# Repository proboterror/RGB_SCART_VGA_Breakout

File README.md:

# JVC TM-1011G RGB SCART / VGA Breakout with S-Video

For RGB/SCART modding JVC, SONY PVM video monitors and consumer CRT TVs.

Modified version for JVC TM-1011G.

- Adjusted board mounting holes / layout.
- Added S-Video (Mini-DIN 4 pin) optional connector with 510 Ohm load resistors.
- Removed CSYNC load resistors / capacitor / solder jumper. CSYNC directly connected to output.

Continuation of [RGB SCART Breakout board](https://github.com/proboterror/RGB_SCART_Breakout).

Features:
- SCART / VGA inputs are not switchable. Simultaneous connection are NOT RECOMMENDED, use at own risk.
- Protection diodes on SCART Blanking / VGA +5V inputs against back current with 2 devices connected.
- 3.5 mm mini jack connector for SCART input.
- Optional S-Video connector.

## Schematics:<br>

## Board view:<br>

## Bill of Materials
|Reference|Value|Footprint|Qty|
|-----|-----|-----|-----|
|C1,C2,C3|100nF|0805|3|
|D1,D2|BAT54W|Diode_SMD:D_SOD-123|2|
|J1|SCART-F|CS-102 (SCART-21S)|1|
|J3|DE15 Socket / DSUB-15-HD / VGA| DSUB-15-HD_Socket_Horizontal P2.29x1.90mm EdgePinOffset3.03mm MountingHolesOffset4.94mm|1|
|J11|SJ1-3535NG|CUI/Same Sky Device SJ1-3535NG|1|
|R1,R2,R3|0R/24R/30R|0805|3|
|R6,R7,R8|75R/51R|0805|3|
|R9,R10|510R|0805|2|
|J2|Mini-DIN 4 pin socket||1|
|R11|1K/1K2/4K7|0805|1|
|R12|2.3K/2K8/10K|0805|1|

Notes:
- All resistors are 1%.
- RGB termination / voltage divider resistors values are depending on monitor jungle (chroma/deflection) IC.<br>
For jungle ICs with 0.7Vpp RGB inputs (like TDA8366):<br>
R1, R2, R3: 0 Ohm,<br>
R6, R7, R8: 75 Ohm.<br>
For jungle ICs with 0.5Vpp RGB inputs (like TA1276AN):<br>
R1, R2, R3: 30 Ohm,<br>
R6, R7, R8: 75 Ohm.<br>
Attenuation / divider resistors R1, R2, R3 can be changed to 24 Ohm, and termination resistors R6, R7, R8 to 51 Ohm for "proper" 75 Ohm termination.
- Blanking voltage divider / pulldown resistors values are depends on jungle IC requirements.<br>
For 3V inputs use R11=1K/1.2K, R12=2.3K/2.8K, and so on.<br>
Some ICs require pulldown R12=10~50K.<br>
R12 can be omitted but R11=120R~180R is recommended to limit current.
- More info on Blanking voltage divider: [sector.sunthar.com/guides/crt-rgb-mod](https://sector.sunthar.com/guides/crt-rgb-mod/rgb-mux.html#how-to-use-the-voltage-divider-on-the-board)

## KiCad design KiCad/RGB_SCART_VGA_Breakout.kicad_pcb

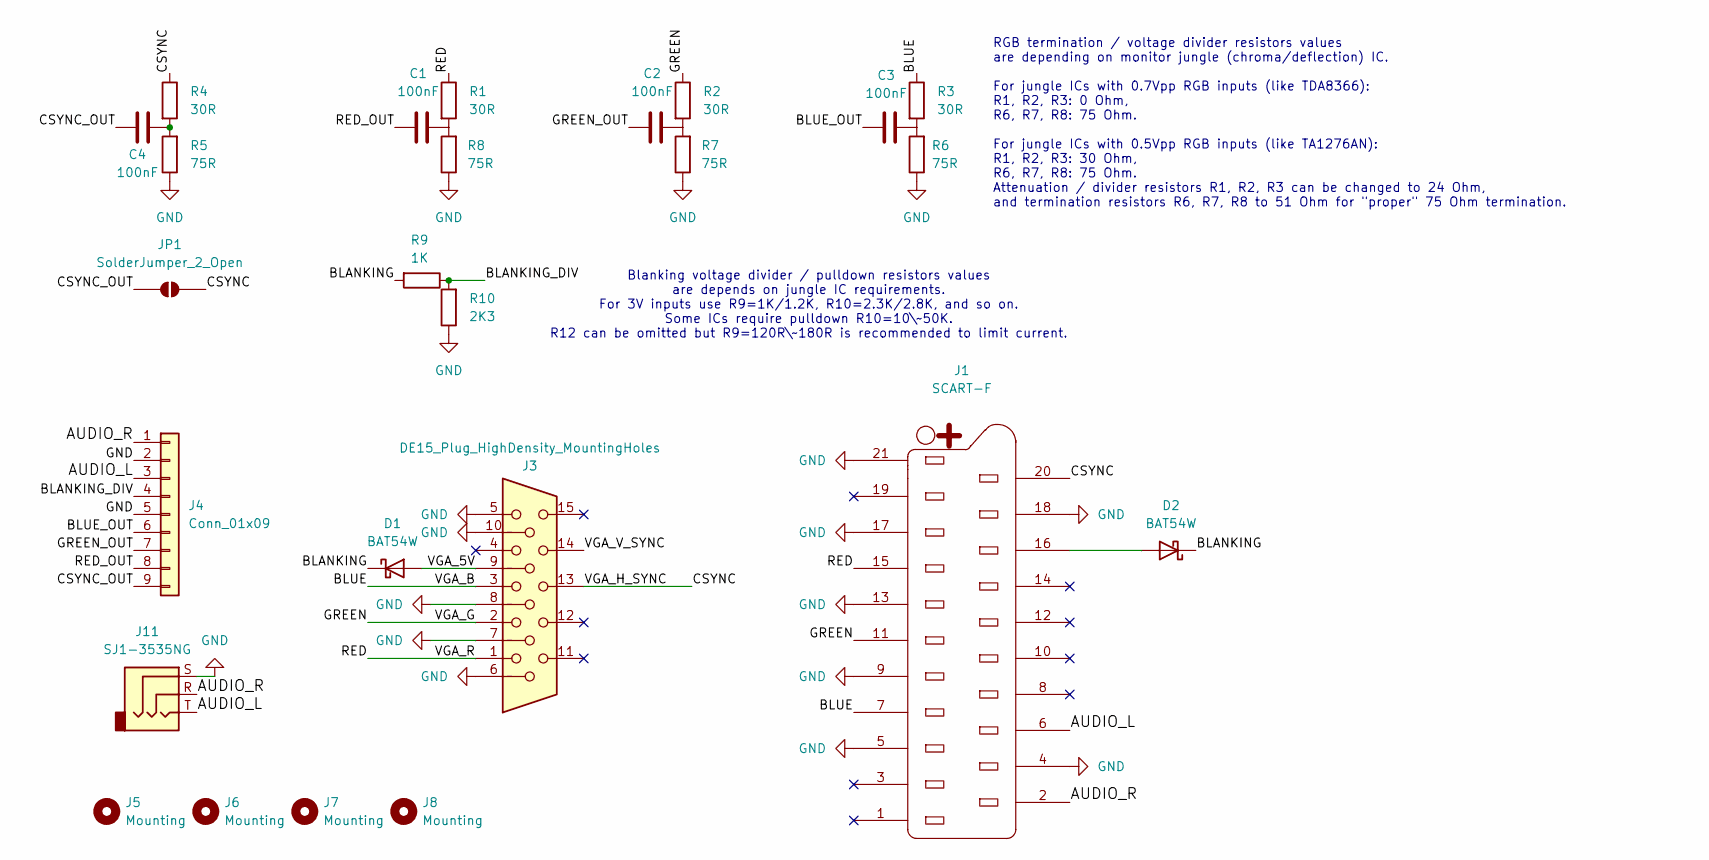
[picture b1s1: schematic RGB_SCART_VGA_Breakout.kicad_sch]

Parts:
C1, C2, C3, C4: 100nF; C_0805_2012Metric
D1, D2: BAT54W; D_SOD-123
J1: SCART-F; K-SCARTX-024
J3: DE15_Plug_HighDensity_MountingHoles; DSUB-15-HD_Socket_Horizontal_P2.29x1.90mm_EdgePinOffset3.03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
J4: Conn_01x09; PinHeader_1x09_P2.54mm_Vertical
J5, J6, J7, J8: Mounting; MountingHole_3.2mm_M3_DIN965_Pad
J11: SJ1-3535NG; Jack_3.5mm_CUI_SJ1-3535NG_Horizontal
JP1: SolderJumper_2_Open; SolderJumper-2_P1.3mm_Open_RoundedPad1.0x1.5mm
R1, R2, R3, R4: 30R; R_0805_2012Metric
R5, R6, R7, R8: 75R; R_0805_2012Metric
R9: 1K; R_0805_2012Metric
R10: 2K3; R_0805_2012Metric

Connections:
/AUDIO_L: J1.6, J4.3, J11.T
/AUDIO_R: J1.2, J4.1, J11.R
/BLANKING: D1.1 (K), D2.1 (K), R9.2
/BLANKING_DIV: J4.4, R9.1, R10.2
/BLUE: J1.7, J3.3, R3.1
/BLUE_OUT: C3.1, J4.6
/CSYNC: J1.20, J3.13, JP1.2 (B), R4.1
/CSYNC_OUT: C4.1, J4.9, JP1.1 (A)
/GREEN: J1.11, J3.2, R2.1
/GREEN_OUT: C2.1, J4.7
/RED: J1.15, J3.1, R1.1
/RED_OUT: C1.1, J4.8
/VGA_5V: D1.2 (A), J3.9
/VGA_V_SYNC: J3.14
GND: J1.4, J1.5, J1.9, J1.13, J1.17, J1.18, J1.21, J3.5, J3.6, J3.7, J3.8, J3.10, J4.2, J4.5, J11.S, R5.1, R6.1, R7.1, R8.1, R10.1
unnamed: C1.2, R1.2, R8.2
unnamed: C2.2, R2.2, R7.2
unnamed: C3.2, R3.2, R6.2
unnamed: C4.2, R4.2, R5.2
unnamed: D2.2 (A), J1.16

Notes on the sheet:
RGB termination / voltage divider resistors values are depending on monitor jungle (chroma/deflection) IC. For jungle ICs with 0.7Vpp RGB inputs (like TDA8366): R1, R2, R3: 0 Ohm, R6, R7, R8: 75 Ohm. For jungle ICs with 0.5Vpp RGB inputs (like TA1276AN): R1, R2, R3: 30 Ohm, R6, R7, R8: 75 Ohm. Atte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
Blanking voltage divider / pulldown resistors values are depends on jungle IC requirements. For 3V inputs use R9=1K/1.2K, R10=2.3K/2.8K, and so on. Some ICs require pulldown R10=10\~50K. R12 can be omitted but R9=120R\~180R is recommended to limit current.

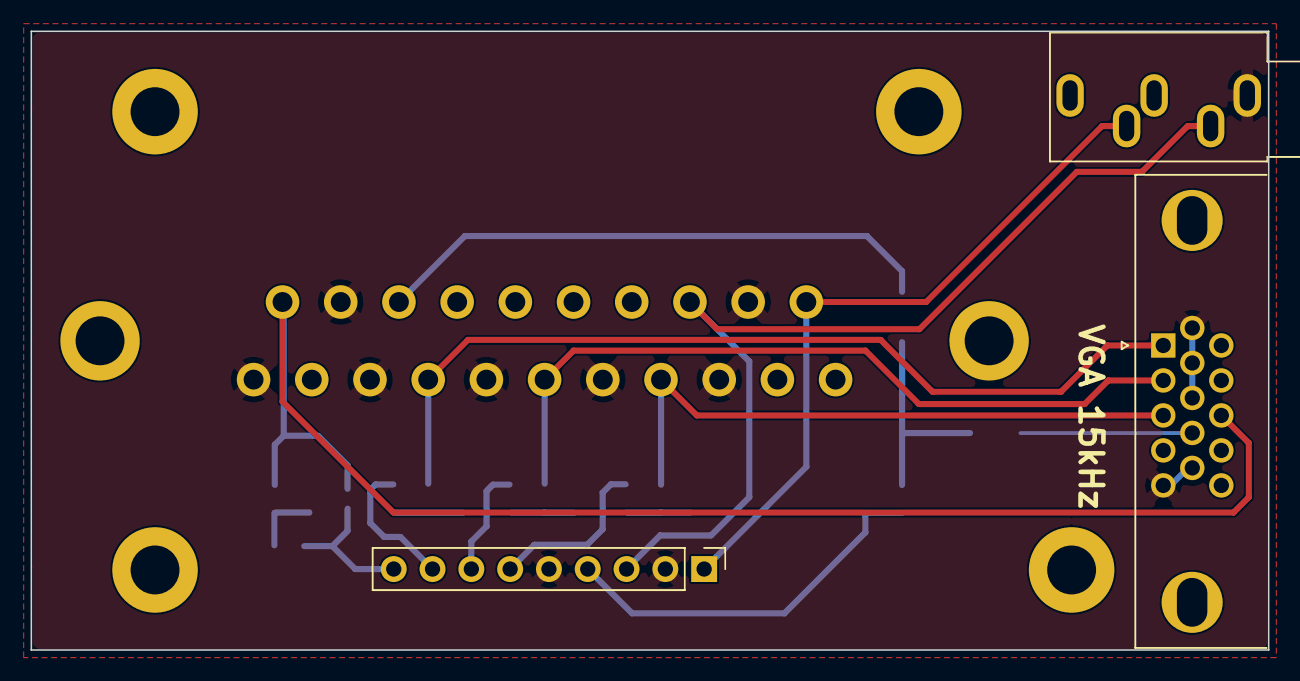
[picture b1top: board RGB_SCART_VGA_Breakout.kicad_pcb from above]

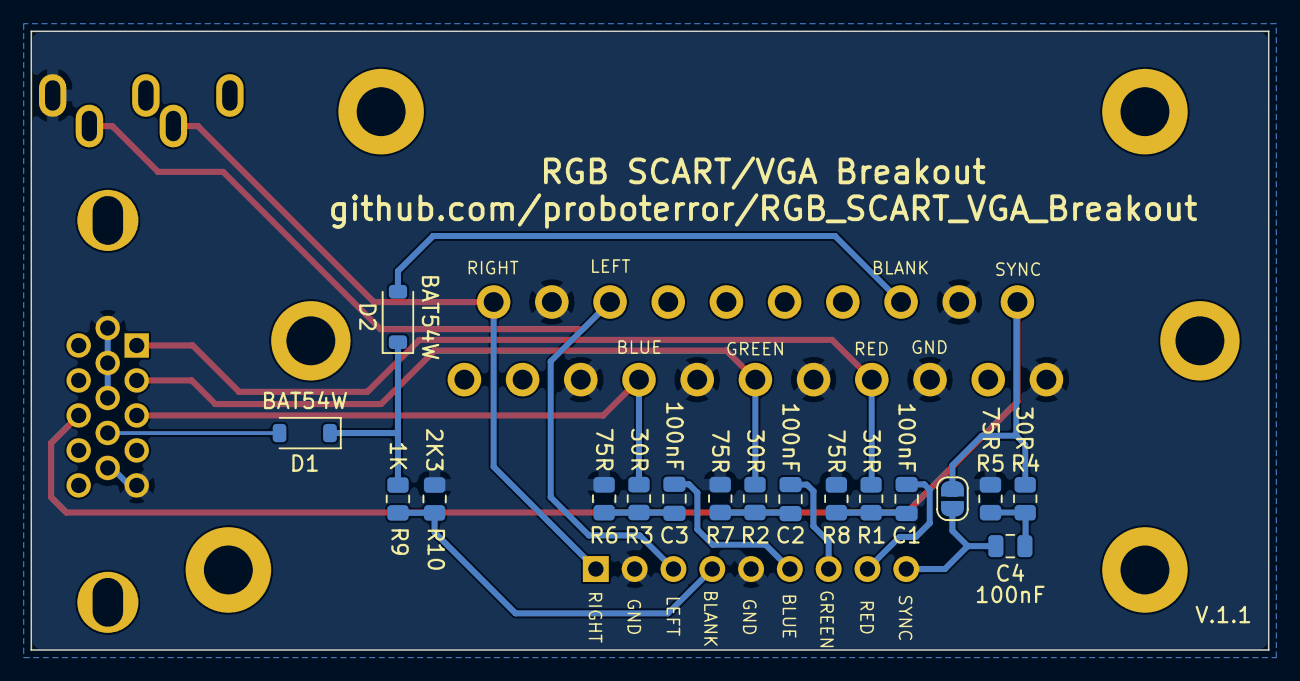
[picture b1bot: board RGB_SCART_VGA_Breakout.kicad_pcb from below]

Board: 2 copper layers, 81.0 x 40.5 mm, 25 parts (17 on the bottom side), 19 nets.

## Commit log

2026-05-02 Initial implementation.
2026-05-02 Update README.md.
2026-05-27 Fixed DE15/VGA connector pinout.
2026-05-27 Update description images.
2026-06-12 Implement SCART/VGA/S-Video breakout board for JVC TM-1011G RGB/S-Video mod.
    MiniDIN 4 pin connector 3D model obtained from https://grabcad.com/library/din-4-pin-connector-2
    MiniDIN 4 pin connector footprint edited from MiniDIN 6 pin https://github.com/4x1md/kicad_libraries/blob/master/Custom_Footprints.pretty/Connector_Mini-DIN_Female_6Pin_2rows.kicad_mod
2026-06-18 Added blanking voltage divider / pulldown resistors with description. Expanded RGB load / voltage divider resistors description.
    PCB version 1.1.
2026-06-19 Added blanking voltage divider / pulldown resistors with description. Expanded RGB load / voltage divider resistors description. VGA pins 7,8,10 connected to GND.
    PCB version 1.1.
